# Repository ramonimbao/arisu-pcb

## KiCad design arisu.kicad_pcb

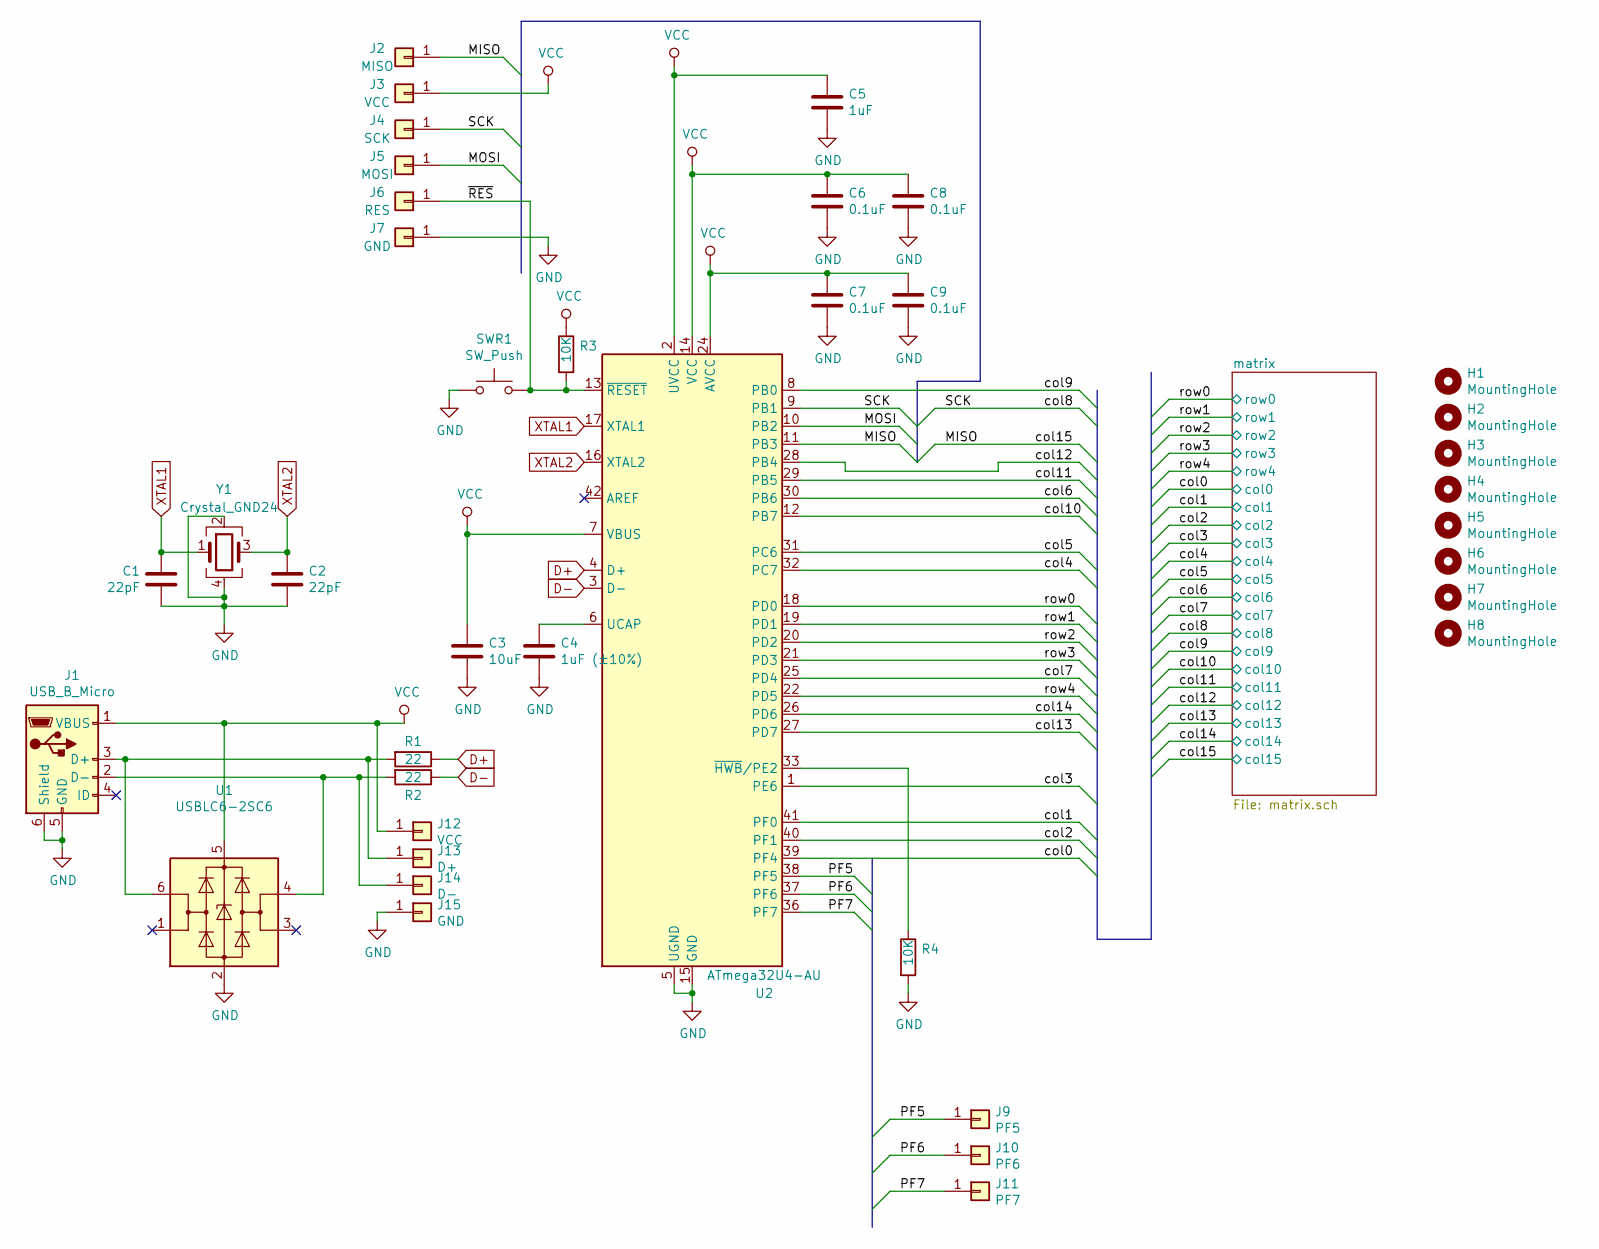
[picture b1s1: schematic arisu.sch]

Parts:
C1, C2: 22pF; C_0805_HandSoldering
C3: 10uF; C_0805_HandSoldering
C4: 1uF (±10%); C_0805_HandSoldering
C5: 1uF; C_0805_HandSoldering
C6, C7, C8, C9: 0.1uF; C_0805_HandSoldering
H1, H2, H3, H4, H5, H6, H7, H8: MountingHole; MountingHole_2.2mm_M2_Pad
J1: USB_B_Micro; USB_Micro-B_Molex-105017-0001
J2: MISO; Pin_Header_Straight_1x01_Pitch2.54mm
J3, J12: VCC; Pin_Header_Straight_1x01_Pitch2.54mm
J4: SCK; Pin_Header_Straight_1x01_Pitch2.54mm
J5: MOSI; Pin_Header_Straight_1x01_Pitch2.54mm
J6: RES; Pin_Header_Straight_1x01_Pitch2.54mm
J7, J15: GND; Pin_Header_Straight_1x01_Pitch2.54mm
J9: PF5; Pin_Header_Straight_1x01_Pitch2.54mm
J10: PF6; Pin_Header_Straight_1x01_Pitch2.54mm
J11: PF7; Pin_Header_Straight_1x01_Pitch2.54mm
J13: D+; Pin_Header_Straight_1x01_Pitch2.54mm
J14: D-; Pin_Header_Straight_1x01_Pitch2.54mm
R1, R2: 22; R_0805_HandSoldering
R3, R4: 10K; R_0805_HandSoldering
SWR1: SW_Push; SW_SPST_TL3342
U1: USBLC6-2SC6; SOT-23-6_Handsoldering
U2: ATmega32U4-AU; TQFP-44_10x10mm_Pitch0.8mm
Y1: Crystal_GND24; Crystal_SMD_SeikoEpson_FA238-4pin_3.2x2.5mm_HandSoldering

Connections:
/MISO: J2.1, U2.11 (PB3); also elsewhere on the board
/MOSI: J5.1, U2.10 (PB2)
/PF5: J9.1, U2.38 (PF5)
/PF6: J10.1, U2.37 (PF6)
/PF7: J11.1, U2.36 (PF7)
/SCK: J4.1, U2.9 (PB1); also elsewhere on the board
/col0: U2.39 (PF4); also elsewhere on the board
/col1: U2.41 (PF0); also elsewhere on the board
/col2: U2.40 (PF1); also elsewhere on the board
/col3: U2.1 (PE6); also elsewhere on the board
/col4: U2.32 (PC7); also elsewhere on the board
/col5: U2.31 (PC6); also elsewhere on the board
/col6: U2.30 (PB6); also elsewhere on the board
/col7: U2.25 (PD4); also elsewhere on the board
/col9: U2.8 (PB0); also elsewhere on the board
/col10: U2.12 (PB7); also elsewhere on the board
/col11: U2.29 (PB5); also elsewhere on the board
/col12: U2.28 (PB4); also elsewhere on the board
/col13: U2.27 (PD7); also elsewhere on the board
/col14: U2.26 (PD6); also elsewhere on the board
/row0: U2.18 (PD0); also elsewhere on the board
/row1: U2.19 (PD1); also elsewhere on the board
/row2: U2.20 (PD2); also elsewhere on the board
/row3: U2.21 (PD3); also elsewhere on the board
/row4: U2.22 (PD5); also elsewhere on the board
/~RES~: J6.1, R3.2, SWR1.2, U2.13 (~RESET)
D+: R1.1, U2.4 (D+)
D-: R2.1, U2.3 (D-)
GND: C1.1, C2.2, C3.2, C4.2, C5.2, C6.2, C7.2, C8.2, C9.2, J1.5 (GND), J1.6 (Shield), J7.1, J15.1, R4.2, SWR1.1, U1.2 (GND), U2.5 (UGND), U2.15 (GND), U2.23 (GND), U2.35 (GND), U2.43 (GND), Y1.2, Y1.4
unnamed: C4.1, U2.6 (UCAP)
unnamed: J1.2 (D-), J14.1, R2.2, U1.4 (I/O2)
unnamed: J1.3 (D+), J13.1, R1.2, U1.6 (I/O1)
unnamed: R4.1, U2.33 (~HWB~/PE2)
VCC: C3.1, C5.1, C6.1, C7.1, C8.1, C9.1, J1.1 (VBUS), J3.1, J12.1, R3.1, U1.5 (VBUS), U2.2 (UVCC), U2.7 (VBUS), U2.14 (VCC), U2.24 (AVCC), U2.34 (VCC), U2.44 (AVCC)
XTAL1: C1.2, U2.17 (XTAL1), Y1.1
XTAL2: C2.1, U2.16 (XTAL2), Y1.3

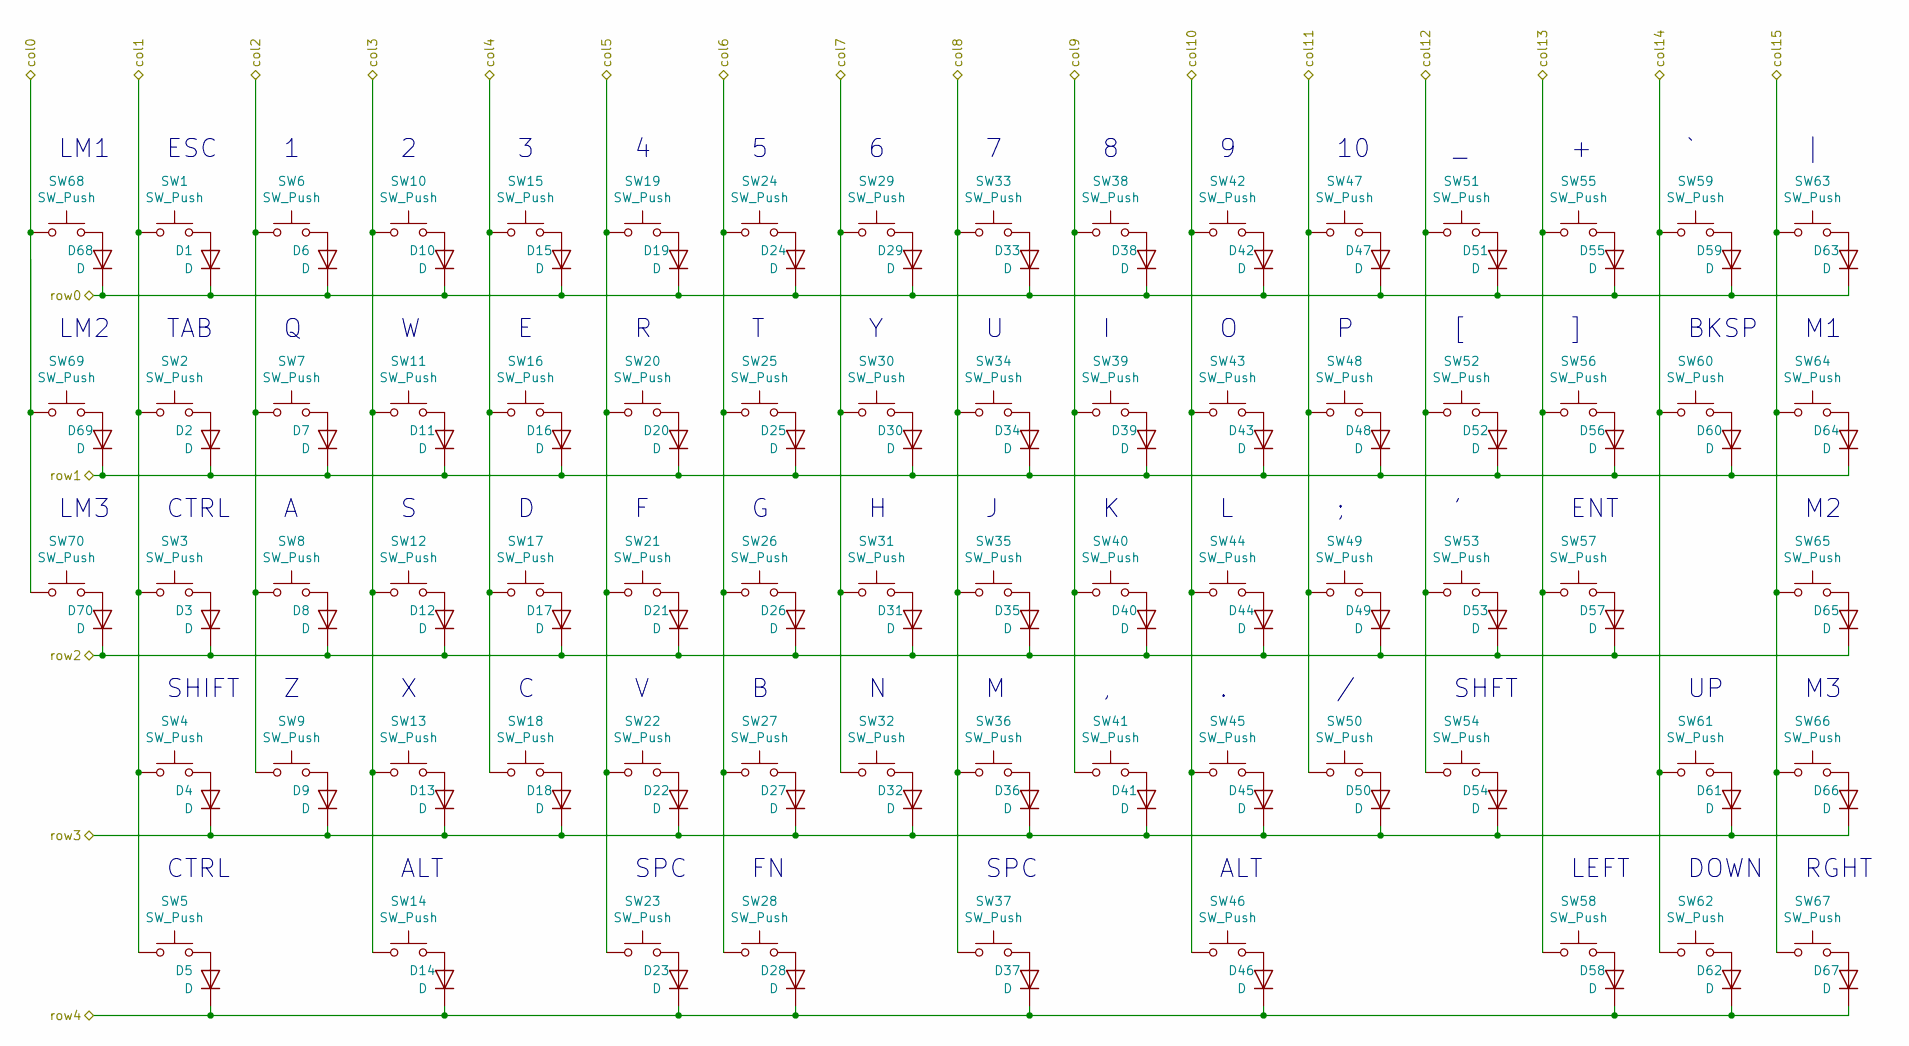
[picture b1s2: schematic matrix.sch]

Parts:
D1, D2, D3, D4, D5, D6, D7, D8, D9, D10, D11, D12, D13, D14, D15, D16, D17, D18, D19, D20, D21, D22, D23, D24, D25, D26, D27, D28, D29, D30, D31, D32, D33, D34, D35, D36, D37, D38, D39, D40, D41, D42, D43, D44, D45, D46, D47, D48, D49, D50, D51, D52, D53, D54, D55, D56, D57, D58, D59, D60, D61, D62, D63, D64, D65, D66, D67, D68, D69, D70: D; D_SOD-123
SW1, SW6, SW7, SW8, SW9, SW10, SW11, SW12, SW13, SW15, SW16, SW17, SW18, SW19, SW20, SW21, SW22, SW24, SW25, SW26, SW27, SW28, SW29, SW30, SW31, SW32, SW33, SW34, SW35, SW36, SW38, SW39, SW40, SW41, SW42, SW43, SW44, SW45, SW47, SW48, SW49, SW50, SW51, SW52, SW53, SW55, SW56, SW58, SW59, SW61, SW62, SW63, SW64, SW65, SW66, SW67, SW68, SW69, SW70: SW_Push; SW_Cherry_MX_1.00u_PCB
SW2, SW5, SW14, SW46, SW60: SW_Push; SW_Cherry_MX_1.50u_PCB
SW3, SW54: SW_Push; SW_Cherry_MX_1.75u_PCB
SW4: SW_Push; SW_Cherry_MX_2.25u_PCB
SW23: SW_Push; SW_Cherry_MX_2.00u_PCB_ReversedStabilizers
SW37: SW_Push; SW_Cherry_MX_2.75u_PCB_ReversedStabilizers
SW57: SW_Push; SW_Cherry_MX_2.25u_PCB_ReversedStabilizers

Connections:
/MISO: SW63.1, SW64.1, SW65.1, SW66.1, SW67.1; also elsewhere on the board
/SCK: SW33.1, SW34.1, SW35.1, SW36.1, SW37.1; also elsewhere on the board
/col0: SW68.1, SW69.1, SW70.1; also elsewhere on the board
/col1: SW1.1, SW2.1, SW3.1, SW4.1, SW5.1; also elsewhere on the board
/col2: SW6.1, SW7.1, SW8.1, SW9.1; also elsewhere on the board
/col3: SW10.1, SW11.1, SW12.1, SW13.1, SW14.1; also elsewhere on the board
/col4: SW15.1, SW16.1, SW17.1, SW18.1; also elsewhere on the board
/col5: SW19.1, SW20.1, SW21.1, SW22.1, SW23.1; also elsewhere on the board
/col6: SW24.1, SW25.1, SW26.1, SW27.1, SW28.1; also elsewhere on the board
/col7: SW29.1, SW30.1, SW31.1, SW32.1; also elsewhere on the board
/col9: SW38.1, SW39.1, SW40.1, SW41.1; also elsewhere on the board
/col10: SW42.1, SW43.1, SW44.1, SW45.1, SW46.1; also elsewhere on the board
/col11: SW47.1, SW48.1, SW49.1, SW50.1; also elsewhere on the board
/col12: SW51.1, SW52.1, SW53.1, SW54.1; also elsewhere on the board
/col13: SW55.1, SW56.1, SW57.1, SW58.1; also elsewhere on the board
/col14: SW59.1, SW60.1, SW61.1, SW62.1; also elsewhere on the board
/row0: D1.1 (K), D6.1 (K), D10.1 (K), D15.1 (K), D19.1 (K), D24.1 (K), D29.1 (K), D33.1 (K), D38.1 (K), D42.1 (K), D47.1 (K), D51.1 (K), D55.1 (K), D59.1 (K), D63.1 (K), D68.1 (K); also elsewhere on the board
/row1: D2.1 (K), D7.1 (K), D11.1 (K), D16.1 (K), D20.1 (K), D25.1 (K), D30.1 (K), D34.1 (K), D39.1 (K), D43.1 (K), D48.1 (K), D52.1 (K), D56.1 (K), D60.1 (K), D64.1 (K), D69.1 (K); also elsewhere on the board
/row2: D3.1 (K), D8.1 (K), D12.1 (K), D17.1 (K), D21.1 (K), D26.1 (K), D31.1 (K), D35.1 (K), D40.1 (K), D44.1 (K), D49.1 (K), D53.1 (K), D57.1 (K), D65.1 (K), D70.1 (K); also elsewhere on the board
/row3: D4.1 (K), D9.1 (K), D13.1 (K), D18.1 (K), D22.1 (K), D27.1 (K), D32.1 (K), D36.1 (K), D41.1 (K), D45.1 (K), D50.1 (K), D54.1 (K), D61.1 (K), D66.1 (K); also elsewhere on the board
/row4: D5.1 (K), D14.1 (K), D23.1 (K), D28.1 (K), D37.1 (K), D46.1 (K), D58.1 (K), D62.1 (K), D67.1 (K); also elsewhere on the board
unnamed: D1.2 (A), SW1.2
unnamed: D2.2 (A), SW2.2
unnamed: D3.2 (A), SW3.2
unnamed: D4.2 (A), SW4.2
unnamed: D5.2 (A), SW5.2
unnamed: D6.2 (A), SW6.2
unnamed: D7.2 (A), SW7.2
unnamed: D8.2 (A), SW8.2
unnamed: D9.2 (A), SW9.2
unnamed: D10.2 (A), SW10.2
unnamed: D11.2 (A), SW11.2
unnamed: D12.2 (A), SW12.2
unnamed: D13.2 (A), SW13.2
unnamed: D14.2 (A), SW14.2
unnamed: D15.2 (A), SW15.2
unnamed: D16.2 (A), SW16.2
unnamed: D17.2 (A), SW17.2
unnamed: D18.2 (A), SW18.2
unnamed: D19.2 (A), SW19.2
unnamed: D20.2 (A), SW20.2
unnamed: D21.2 (A), SW21.2
unnamed: D22.2 (A), SW22.2
unnamed: D23.2 (A), SW23.2
unnamed: D24.2 (A), SW24.2
unnamed: D25.2 (A), SW25.2
unnamed: D26.2 (A), SW26.2
unnamed: D27.2 (A), SW27.2
unnamed: D28.2 (A), SW28.2
unnamed: D29.2 (A), SW29.2
unnamed: D30.2 (A), SW30.2
unnamed: D31.2 (A), SW31.2
unnamed: D32.2 (A), SW32.2
unnamed: D33.2 (A), SW33.2
unnamed: D34.2 (A), SW34.2
unnamed: D35.2 (A), SW35.2
unnamed: D36.2 (A), SW36.2
unnamed: D37.2 (A), SW37.2
unnamed: D38.2 (A), SW38.2
unnamed: D39.2 (A), SW39.2
unnamed: D40.2 (A), SW40.2
unnamed: D41.2 (A), SW41.2
unnamed: D42.2 (A), SW42.2
unnamed: D43.2 (A), SW43.2
unnamed: D44.2 (A), SW44.2
unnamed: D45.2 (A), SW45.2
unnamed: D46.2 (A), SW46.2
unnamed: D47.2 (A), SW47.2
unnamed: D48.2 (A), SW48.2
unnamed: D49.2 (A), SW49.2
unnamed: D50.2 (A), SW50.2
unnamed: D51.2 (A), SW51.2
unnamed: D52.2 (A), SW52.2
unnamed: D53.2 (A), SW53.2
unnamed: D54.2 (A), SW54.2
unnamed: D55.2 (A), SW55.2
unnamed: D56.2 (A), SW56.2
unnamed: D57.2 (A), SW57.2
unnamed: D58.2 (A), SW58.2
unnamed: D59.2 (A), SW59.2
unnamed: D60.2 (A), SW60.2
unnamed: D61.2 (A), SW61.2
unnamed: D62.2 (A), SW62.2
unnamed: D63.2 (A), SW63.2
unnamed: D64.2 (A), SW64.2
unnamed: D65.2 (A), SW65.2
unnamed: D66.2 (A), SW66.2
unnamed: D67.2 (A), SW67.2
unnamed: D68.2 (A), SW68.2
unnamed: D69.2 (A), SW69.2
unnamed: D70.2 (A), SW70.2

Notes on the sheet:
ESC
TAB
BKSP
CTRL
ENT
SHIFT
SHFT
ALT
SPC
DOWN
LEFT
RGHT
LM1
LM2
LM3

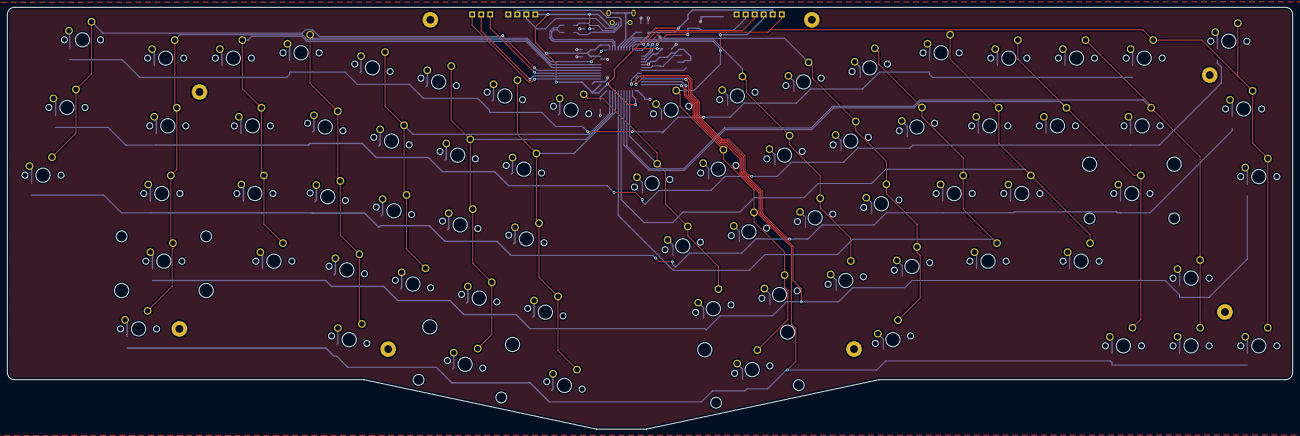
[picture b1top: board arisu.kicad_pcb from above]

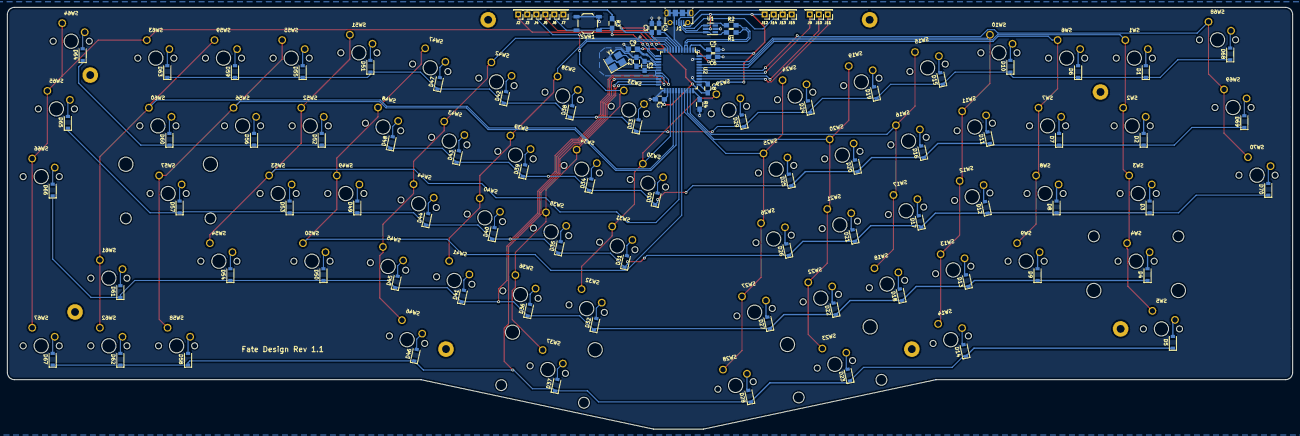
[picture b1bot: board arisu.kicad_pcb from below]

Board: 2 copper layers, 361.7 x 118.7 mm, 179 parts (101 on the bottom side), 106 nets.

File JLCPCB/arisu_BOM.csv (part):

Reference, Value, Footprint, Datasheet
"U2","ATmega32U4-AU","Housings_QFP:TQFP-44_10x10mm_Pitch0.8mm","http://ww1.microchip.com/downloads/en/DeviceDoc/Atmel-7766-8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"
"J1","USB_B_Micro","Connectors_USB:USB_Micro-B_Molex-105017-0001","~"
"U1","USBLC6-2SC6","TO_SOT_Packages_SMD:SOT-23-6_Handsoldering","http://www2.st.com/resource/en/datasheet/CD00050750.pdf"
"R1","22","Resistors_SMD:R_0805_HandSoldering","~"
"R2","22","Resistors_SMD:R_0805_HandSoldering","~"
"C4","1uF (±10%)","Capacitors_SMD:C_0805_HandSoldering","~"
"Y1","Crystal_GND24","Crystals:Crystal_SMD_SeikoEpson_FA238-4pin_3.2x2.5mm_HandSoldering","~"
"C1","22pF","Capacitors_SMD:C_0805_HandSoldering","~"
"C2","22pF","Capacitors_SMD:C_0805_HandSoldering","~"
"C3","10uF","Capacitors_SMD:C_0805_HandSoldering","~"
"SWR1","SW_Push","Buttons_Switches_SMD:SW_SPST_TL3342",""
"R3","10K","Resistors_SMD:R_0805_HandSoldering","~"
"C5","1uF","Capacitors_SMD:C_0805_HandSoldering","~"
"C6","0.1uF","Capacitors_SMD:C_0805_HandSoldering","~"
"C8","0.1uF","Capacitors_SMD:C_0805_HandSoldering","~"
"C7","0.1uF","Capacitors_SMD:C_0805_HandSoldering","~"
"C9","0.1uF","Capacitors_SMD:C_0805_HandSoldering","~"
"R4","10K","Resistors_SMD:R_0805_HandSoldering","~"
"J9","PF5","Pin_Headers:Pin_Header_Straight_1x01_Pitch2.54mm","~"
"J10","PF6","Pin_Headers:Pin_Header_Straight_1x01_Pitch2.54mm","~"
"J11","PF7","Pin_Headers:Pin_Header_Straight_1x01_Pitch2.54mm","~"
"J2","MISO","Pin_Headers:Pin_Header_Straight_1x01_Pitch2.54mm","~"
"J3","VCC","Pin_Headers:Pin_Header_Straight_1x01_Pitch2.54mm","~"
"J4","SCK","Pin_Headers:Pin_Header_Straight_1x01_Pitch2.54mm","~"
"J5","MOSI","Pin_Headers:Pin_Header_Straight_1x01_Pitch2.54mm","~"
"J6","RES","Pin_Headers:Pin_Header_Straight_1x01_Pitch2.54mm","~"
"J7","GND","Pin_Headers:Pin_Header_Straight_1x01_Pitch2.54mm","~"
"J13","D+","Pin_Headers:Pin_Header_Straight_1x01_Pitch2.54mm","~"
"J14","D-","Pin_Headers:Pin_Header_Straight_1x01_Pitch2.54mm","~"
"J12","VCC","Pin_Headers:Pin_Header_Straight_1x01_Pitch2.54mm","~"
"J15","GND","Pin_Headers:Pin_Header_Straight_1x01_Pitch2.54mm","~"
"H1","MountingHole","Mounting_Holes:MountingHole_2.2mm_M2_Pad","~"
"H2","MountingHole","Mounting_Holes:MountingHole_2.2mm_M2_Pad","~"
"H3","MountingHole","Mounting_Holes:MountingHole_2.2mm_M2_Pad","~"
"H4","MountingHole","Mounting_Holes:MountingHole_2.2mm_M2_Pad","~"
"H5","MountingHole","Mounting_Holes:MountingHole_2.2mm_M2_Pad","~"
"H6","MountingHole","Mounting_Holes:MountingHole_2.2mm_M2_Pad","~"
"H7","MountingHole","Mounting_Holes:MountingHole_2.2mm_M2_Pad","~"
"H8","MountingHole","Mounting_Holes:MountingHole_2.2mm_M2_Pad","~"
"SW1","SW_Push","MX_Switch:SW_Cherry_MX_1.00u_PCB",""
"D1","D","Diodes_SMD:D_SOD-123","~"
"SW6","SW_Push","MX_Switch:SW_Cherry_MX_1.00u_PCB",""
"SW2","SW_Push","MX_Switch:SW_Cherry_MX_1.50u_PCB",""
"D2","D","Diodes_SMD:D_SOD-123","~"
"D6","D","Diodes_SMD:D_SOD-123","~"
"SW7","SW_Push","MX_Switch:SW_Cherry_MX_1.00u_PCB",""
"D7","D","Diodes_SMD:D_SOD-123","~"
"SW3","SW_Push","MX_Switch:SW_Cherry_MX_1.75u_PCB",""
"D3","D","Diodes_SMD:D_SOD-123","~"
"SW4","SW_Push","MX_Switch:SW_Cherry_MX_2.25u_PCB",""
"SW5","SW_Push","MX_Switch:SW_Cherry_MX_1.50u_PCB",""
"D4","D","Diodes_SMD:D_SOD-123","~"
"D5","D","Diodes_SMD:D_SOD-123","~"
"SW8","SW_Push","MX_Switch:SW_Cherry_MX_1.00u_PCB",""
"SW9","SW_Push","MX_Switch:SW_Cherry_MX_1.00u_PCB",""
"D8","D","Diodes_SMD:D_SOD-123","~"
"D9","D","Diodes_SMD:D_SOD-123","~"
"SW10","SW_Push","MX_Switch:SW_Cherry_MX_1.00u_PCB",""
"D10","D","Diodes_SMD:D_SOD-123","~"
"SW11","SW_Push","MX_Switch:SW_Cherry_MX_1.00u_PCB",""
"D11","D","Diodes_SMD:D_SOD-123","~"
"SW12","SW_Push","MX_Switch:SW_Cherry_MX_1.00u_PCB",""
"SW13","SW_Push","MX_Switch:SW_Cherry_MX_1.00u_PCB",""
"SW14","SW_Push","MX_Switch:SW_Cherry_MX_1.50u_PCB",""
"D12","D","Diodes_SMD:D_SOD-123","~"
"D13","D","Diodes_SMD:D_SOD-123","~"
"D14","D","Diodes_SMD:D_SOD-123","~"
"SW15","SW_Push","MX_Switch:SW_Cherry_MX_1.00u_PCB",""
"D15","D","Diodes_SMD:D_SOD-123","~"
"SW16","SW_Push","MX_Switch:SW_Cherry_MX_1.00u_PCB",""
"D16","D","Diodes_SMD:D_SOD-123","~"
"SW17","SW_Push","MX_Switch:SW_Cherry_MX_1.00u_PCB",""
"SW18","SW_Push","MX_Switch:SW_Cherry_MX_1.00u_PCB",""
"D17","D","Diodes_SMD:D_SOD-123","~"
"D18","D","Diodes_SMD:D_SOD-123","~"
"SW19","SW_Push","MX_Switch:SW_Cherry_MX_1.00u_PCB",""
"D19","D","Diodes_SMD:D_SOD-123","~"
"SW20","SW_Push","MX_Switch:SW_Cherry_MX_1.00u_PCB",""
"D20","D","Diodes_SMD:D_SOD-123","~"
"SW21","SW_Push","MX_Switch:SW_Cherry_MX_1.00u_PCB",""
"SW22","SW_Push","MX_Switch:SW_Cherry_MX_1.00u_PCB",""
"SW23","SW_Push","MX_Switch:SW_Cherry_MX_2.00u_PCB_ReversedStabilizers",""
"D21","D","Diodes_SMD:D_SOD-123","~"
"D22","D","Diodes_SMD:D_SOD-123","~"
"D23","D","Diodes_SMD:D_SOD-123","~"
"SW24","SW_Push","MX_Switch:SW_Cherry_MX_1.00u_PCB",""
"D24","D","Diodes_SMD:D_SOD-123","~"
"SW25","SW_Push","MX_Switch:SW_Cherry_MX_1.00u_PCB",""
"D25","D","Diodes_SMD:D_SOD-123","~"
"SW26","SW_Push","MX_Switch:SW_Cherry_MX_1.00u_PCB",""
"SW27","SW_Push","MX_Switch:SW_Cherry_MX_1.00u_PCB",""
"SW28","SW_Push","MX_Switch:SW_Cherry_MX_1.00u_PCB",""
"D26","D","Diodes_SMD:D_SOD-123","~"
"D27","D","Diodes_SMD:D_SOD-123","~"
"D28","D","Diodes_SMD:D_SOD-123","~"
"SW29","SW_Push","MX_Switch:SW_Cherry_MX_1.00u_PCB",""
"D29","D","Diodes_SMD:D_SOD-123","~"
"SW30","SW_Push","MX_Switch:SW_Cherry_MX_1.00u_PCB",""
"D30","D","Diodes_SMD:D_SOD-123","~"
"SW31","SW_Push","MX_Switch:SW_Cherry_MX_1.00u_PCB",""
"SW32","SW_Push","MX_Switch:SW_Cherry_MX_1.00u_PCB",""
"D31","D","Diodes_SMD:D_SOD-123","~"
"D32","D","Diodes_SMD:D_SOD-123","~"
"SW33","SW_Push","MX_Switch:SW_Cherry_MX_1.00u_PCB",""
"D33","D","Diodes_SMD:D_SOD-123","~"
"SW34","SW_Push","MX_Switch:SW_Cherry_MX_1.00u_PCB",""
"D34","D","Diodes_SMD:D_SOD-123","~"
"SW35","SW_Push","MX_Switch:SW_Cherry_MX_1.00u_PCB",""
"SW36","SW_Push","MX_Switch:SW_Cherry_MX_1.00u_PCB",""
"SW37","SW_Push","MX_Switch:SW_Cherry_MX_2.75u_PCB_ReversedStabilizers",""
"D35","D","Diodes_SMD:D_SOD-123","~"
"D36","D","Diodes_SMD:D_SOD-123","~"
"D37","D","Diodes_SMD:D_SOD-123","~"
"SW38","SW_Push","MX_Switch:SW_Cherry_MX_1.00u_PCB",""
"D38","D","Diodes_SMD:D_SOD-123","~"
"SW39","SW_Push","MX_Switch:SW_Cherry_MX_1.00u_PCB",""
"D39","D","Diodes_SMD:D_SOD-123","~"
"SW40","SW_Push","MX_Switch:SW_Cherry_MX_1.00u_PCB",""
"SW41","SW_Push","MX_Switch:SW_Cherry_MX_1.00u_PCB",""
"D40","D","Diodes_SMD:D_SOD-123","~"
"D41","D","Diodes_SMD:D_SOD-123","~"
"SW42","SW_Push","MX_Switch:SW_Cherry_MX_1.00u_PCB",""
"D42","D","Diodes_SMD:D_SOD-123","~"
"SW43","SW_Push","MX_Switch:SW_Cherry_MX_1.00u_PCB",""
"D43","D","Diodes_SMD:D_SOD-123","~"
"SW44","SW_Push","MX_Switch:SW_Cherry_MX_1.00u_PCB",""
"SW45","SW_Push","MX_Switch:SW_Cherry_MX_1.00u_PCB",""
"SW46","SW_Push","MX_Switch:SW_Cherry_MX_1.50u_PCB",""
"D44","D","Diodes_SMD:D_SOD-123","~"
"D45","D","Diodes_SMD:D_SOD-123","~"
"D46","D","Diodes_SMD:D_SOD-123","~"
"SW47","SW_Push","MX_Switch:SW_Cherry_MX_1.00u_PCB",""
"D47","D","Diodes_SMD:D_SOD-123","~"
"SW48","SW_Push","MX_Switch:SW_Cherry_MX_1.00u_PCB",""
"D48","D","Diodes_SMD:D_SOD-123","~"
"SW49","SW_Push","MX_Switch:SW_Cherry_MX_1.00u_PCB",""
"SW50","SW_Push","MX_Switch:SW_Cherry_MX_1.00u_PCB",""
"D49","D","Diodes_SMD:D_SOD-123","~"
"D50","D","Diodes_SMD:D_SOD-123","~"
"SW51","SW_Push","MX_Switch:SW_Cherry_MX_1.00u_PCB",""
"D51","D","Diodes_SMD:D_SOD-123","~"
"SW52","SW_Push","MX_Switch:SW_Cherry_MX_1.00u_PCB",""
"D52","D","Diodes_SMD:D_SOD-123","~"
"SW53","SW_Push","MX_Switch:SW_Cherry_MX_1.00u_PCB",""
"SW54","SW_Push","MX_Switch:SW_Cherry_MX_1.75u_PCB",""
"D53","D","Diodes_SMD:D_SOD-123","~"
"D54","D","Diodes_SMD:D_SOD-123","~"
"SW55","SW_Push","MX_Switch:SW_Cherry_MX_1.00u_PCB",""
"D55","D","Diodes_SMD:D_SOD-123","~"
"SW56","SW_Push","MX_Switch:SW_Cherry_MX_1.00u_PCB",""
"D56","D","Diodes_SMD:D_SOD-123","~"
"SW57","SW_Push","MX_Switch:SW_Cherry_MX_2.25u_PCB_ReversedStabilizers",""
"SW58","SW_Push","MX_Switch:SW_Cherry_MX_1.00u_PCB",""
"D57","D","Diodes_SMD:D_SOD-123","~"
"D58","D","Diodes_SMD:D_SOD-123","~"
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
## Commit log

2021-05-03 Modify arisu PCB for oncelot#1574
2021-05-03 Finalize sch and pcb
2021-05-03 Generate gerbers and add BOM/CPL files for JLCPCB
2021-05-03 Change .gitignore
